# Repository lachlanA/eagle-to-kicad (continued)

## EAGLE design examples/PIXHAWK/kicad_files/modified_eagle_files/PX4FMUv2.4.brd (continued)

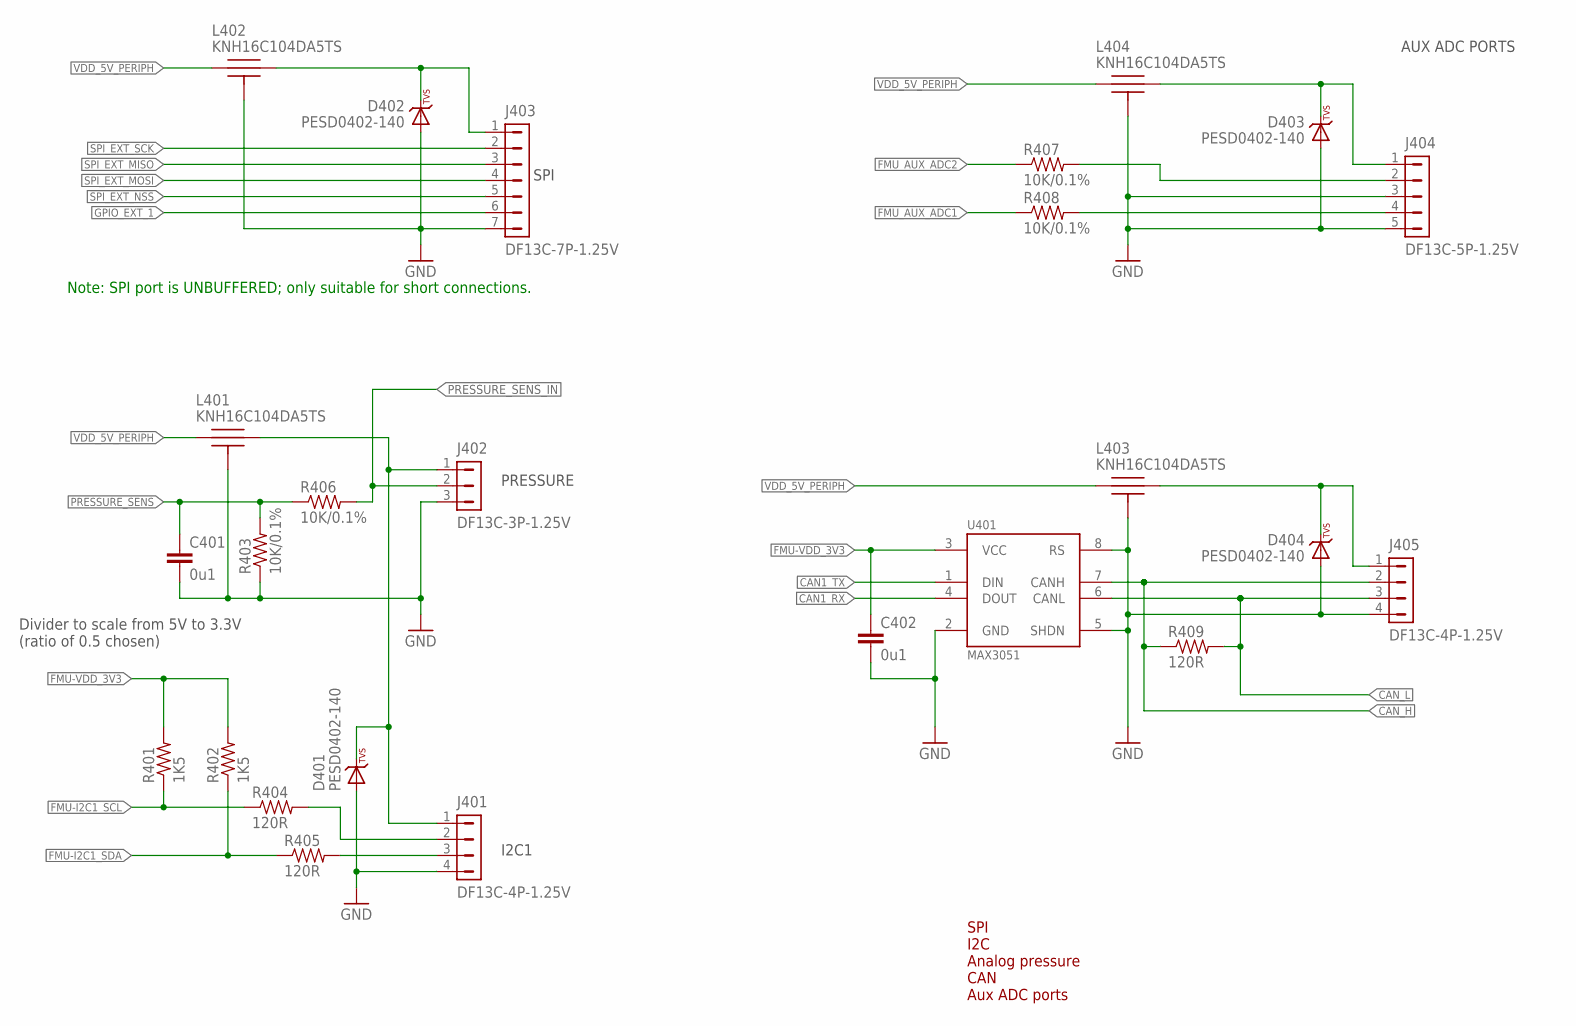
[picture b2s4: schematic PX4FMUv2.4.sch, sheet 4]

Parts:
C401, C402: 0u1; 0402-CAP; PARTNO CC0402ZRY5V7BB104
D401, D402, D403, D404: PESD0402-140; 0402-TVS; PARTNO PESD0402-140
J401, J405: DF13C-4P-1.25V; PARTNO DF13C-4P-1.25V(20)
J402: DF13C-3P-1.25V; PARTNO DF13C-3P-1.25V(20)
J403: DF13C-7P-1.25V; PARTNO DF13C-7P-1.25V(20)
J404: DF13C-5P-1.25V; PARTNO DF13C-5P-1.25V(20)
L401, L402, L403, L404: KNH16C104DA5TS; KYOCERA-KNH16-DA; PARTNO KNH16C104DA5TS
R401, R402: 1K5; 0402-RES; PARTNO RC0402FR-071K5L
R403, R406, R407, R408: 10K/0.1%; 0402-RES; PARTNO ERA-2AEB103X
R404, R405, R409: 120R; 0402-RES; PARTNO RC0402FR-07120RL
U401: MAX3051; SOT23-8; PARTNO MAX3051EKA

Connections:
!SPI_EXT_NSS: J403.5; also elsewhere on the board
CAN1_RX: U401.4 (DOUT); also elsewhere on the board
CAN1_TX: U401.1 (DIN); also elsewhere on the board
CAN_H: J405.2, R409.P$1 (1), U401.7 (CANH); also elsewhere on the board
CAN_L: J405.3, R409.P$2 (2), U401.6 (CANL); also elsewhere on the board
FMU-I2C1_SCL: R401.P$1 (1), R404.P$1 (1); also elsewhere on the board
FMU-I2C1_SDA: R402.P$1 (1), R405.P$1 (1); also elsewhere on the board
FMU-VDD_3V3: C402.P$1 (1), R401.P$2 (2), R402.P$2 (2), U401.3 (VCC); also elsewhere on the board
FMU_AUX_ADC1: R408.P$1 (1); also elsewhere on the board
FMU_AUX_ADC1_PROT: J404.4, R408.P$2 (2)
FMU_AUX_ADC2: R407.P$1 (1); also elsewhere on the board
FMU_AUX_ADC2_PROT: J404.2, R407.P$2 (2)
GND: C401.P$2 (2), C402.P$2 (2), D401.A, D402.A, D403.A, D404.A, J401.4, J402.3, J403.7, J404.3, J404.5, J405.4, L401.P$3, L401.P$4, L401.P$5, L402.P$3, L402.P$4, L402.P$5, L403.P$3, L403.P$4, L403.P$5, L404.P$3, L404.P$4, L404.P$5, R403.P$1 (1), U401.2 (GND), U401.5 (SHDN), U401.8 (RS); also elsewhere on the board
GPIO_EXT_1: J403.6; also elsewhere on the board
unnamed: J401.2, R404.P$2 (2)
unnamed: J401.3, R405.P$2 (2)
unnamed: D402.C, J403.1, L402.P$2
unnamed: D401.C, J401.1, J402.1, L401.P$2
unnamed: D404.C, J405.1, L403.P$2
unnamed: D403.C, J404.1, L404.P$2
PRESSURE_SENS: C401.P$1 (1), R403.P$2 (2), R406.P$1 (1); also elsewhere on the board
PRESSURE_SENS_IN: J402.2, R406.P$2 (2); also elsewhere on the board
SPI_EXT_MISO: J403.3; also elsewhere on the board
SPI_EXT_MOSI: J403.4; also elsewhere on the board
SPI_EXT_SCK: J403.2; also elsewhere on the board
VDD_5V_PERIPH: L401.P$1, L402.P$1, L403.P$1, L404.P$1; also elsewhere on the board

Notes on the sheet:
SPI
PRESSURE
I2C1
AUX ADC PORTS
SPI I2C Analog pressure CAN Aux ADC ports
Note: SPI port is UNBUFFERED; only suitable for short connections.
Divider to scale from 5V to 3.3V (ratio of 0.5 chosen)

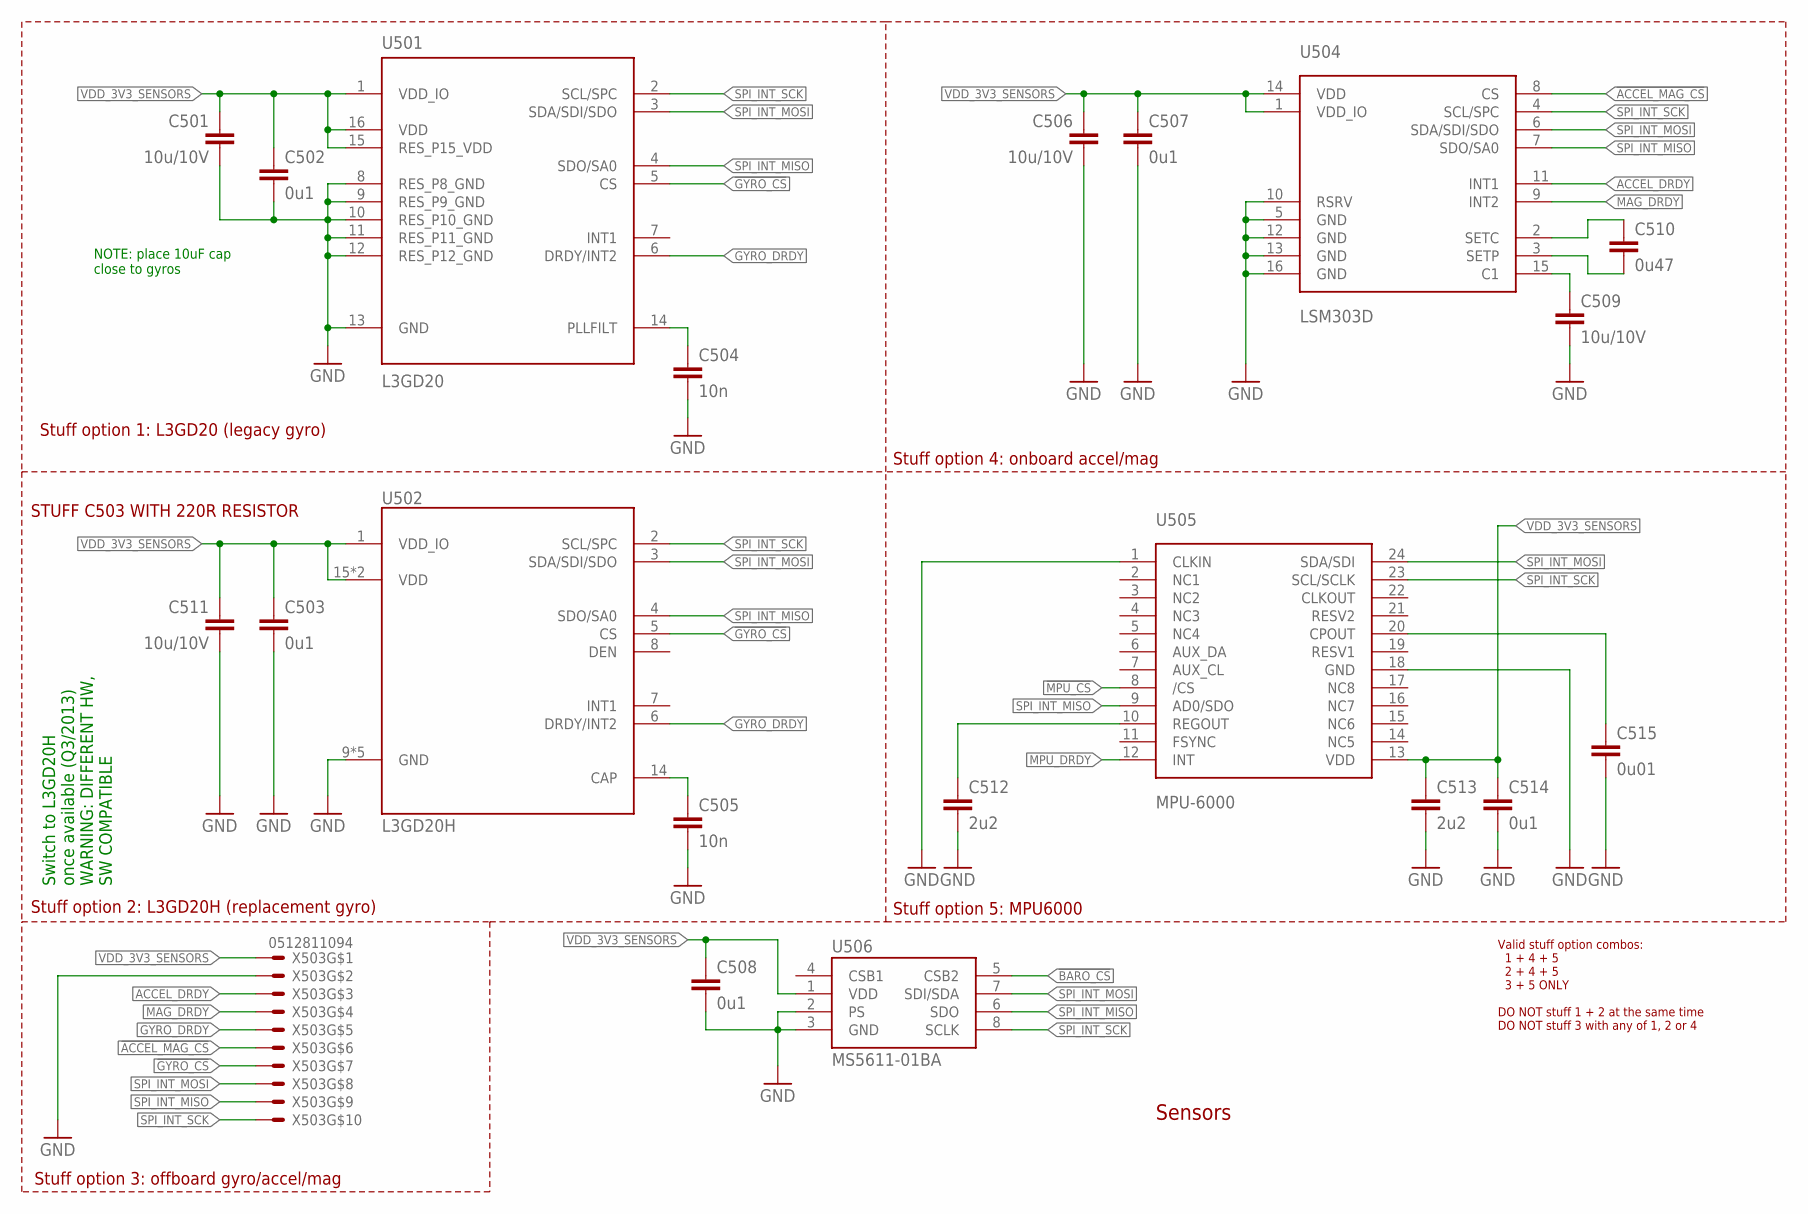
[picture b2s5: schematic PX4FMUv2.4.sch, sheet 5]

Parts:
C501, C506, C509, C511: 10u/10V; 0805-CAP; PARTNO CC0805ZKY5V6BB106
C502, C503, C507, C508, C514: 0u1; 0402-CAP; PARTNO CC0402ZRY5V7BB104
C504, C505: 10n; 0402-CAP; PARTNO CC0402KRX7R7BB103
C510: 0u47; 0402-CAP; PARTNO C1005X5R1C474K050BC
C512, C513: 2u2; 0603-CAP; PARTNO CC0402ZRY5V7BB104
C515: 0u01; 0603-CAP; PARTNO GRM155R71E103JA01J
U501: L3GD20; L3G4200DH-MAN; PARTNO L3GD20
U502: L3GD20H; LGA-16L; PARTNO L3GD20H
U504: LSM303D; LGA-16L; PARTNO LSM303D
U505: MPU-6000; QFN-24; PARTNO MPU-6000
U506: MS5611-01BA; PARTNO MS5611-01BA
X503: 0512811094; 51281-1094; PARTNO 0781191109

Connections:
!ACCEL_MAG_CS: U504.8 (CS), X503.6; also elsewhere on the board
!BARO_CS: U506.5 (CSB2); also elsewhere on the board
!GYRO_CS: U501.5 (CS), U502.5 (CS), X503.7; also elsewhere on the board
!MPU_CS: U505.8 (/CS); also elsewhere on the board
ACCEL_DRDY: U504.11 (INT1), X503.3; also elsewhere on the board
GND: C501.P$2 (2), C502.P$2 (2), C503.P$2 (2), C504.P$2 (2), C505.P$2 (2), C506.P$2 (2), C507.P$2 (2), C508.P$2 (2), C509.P$2 (2), C511.P$2 (2), C512.P$2 (2), C513.P$2 (2), C514.P$2 (2), C515.P$2 (2), U501.8 (RES_P8_GND), U501.9 (RES_P9_GND), U501.10 (RES_P10_GND), U501.11 (RES_P11_GND), U501.12 (RES_P12_GND), U501.13 (GND), U502.9 (GND), U502.10 (GND), U502.11 (GND), U502.12 (GND), U502.13 (GND), U504.5 (GND), U504.10 (RSRV), U504.12 (GND), U504.13 (GND), U504.16 (GND), U505.1 (CLKIN), U505.18 (GND), U506.2 (PS), U506.3 (GND), X503.2; also elsewhere on the board
GYRO_DRDY: U501.6 (DRDY/INT2), U502.6 (DRDY/INT2), X503.5; also elsewhere on the board
MAG_DRDY: U504.9 (INT2), X503.4; also elsewhere on the board
MPU_DRDY: U505.12 (INT); also elsewhere on the board
unnamed: C509.P$1 (1), U504.15 (C1)
unnamed: C510.P$1 (1), U504.2 (SETC)
unnamed: C510.P$2 (2), U504.3 (SETP)
unnamed: C505.P$1 (1), U502.14 (CAP)
unnamed: C504.P$1 (1), U501.14 (PLLFILT)
unnamed: C512.P$1 (1), U505.10 (REGOUT)
unnamed: C515.P$1 (1), U505.20 (CPOUT)
SPI_INT_MISO: U501.4 (SDO/SA0), U502.4 (SDO/SA0), U504.7 (SDO/SA0), U505.9 (AD0/SDO), U506.6 (SDO), X503.9; also elsewhere on the board
SPI_INT_MOSI: U501.3 (SDA/SDI/SDO), U502.3 (SDA/SDI/SDO), U504.6 (SDA/SDI/SDO), U505.24 (SDA/SDI), U506.7 (SDI/SDA), X503.8; also elsewhere on the board
SPI_INT_SCK: U501.2 (SCL/SPC), U502.2 (SCL/SPC), U504.4 (SCL/SPC), U505.23 (SCL/SCLK), U506.8 (SCLK), X503.10; also elsewhere on the board
VDD_3V3_SENSORS: C501.P$1 (1), C502.P$1 (1), C503.P$1 (1), C506.P$1 (1), C507.P$1 (1), C508.P$1 (1), C511.P$1 (1), C513.P$1 (1), C514.P$1 (1), U501.1 (VDD_IO), U501.15 (RES_P15_VDD), U501.16 (VDD), U502.1 (VDD_IO), U502.15 (VDD), U502.16 (VDD), U504.1 (VDD_IO), U504.14 (VDD), U505.13 (VDD), U506.1 (VDD), X503.1; also elsewhere on the board

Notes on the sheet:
Sensors
Switch to L3GD20H once available (Q3/2013) WARNING: DIFFERENT HW, SW COMPATIBLE
NOTE: place 10uF cap close to gyros
Stuff option 1: L3GD20 (legacy gyro)
Stuff option 2: L3GD20H (replacement gyro)
Stuff option 4: onboard accel/mag
Valid stuff option combos: 1 + 4 + 5 2 + 4 + 5 3 + 5 ONLY DO NOT stuff 1 + 2 at the same time DO NOT stuff 3 with any of 1, 2 or 4
Stuff option 5: MPU6000
Stuff option 3: offboard gyro/accel/mag
STUFF C503 WITH 220R RESISTOR

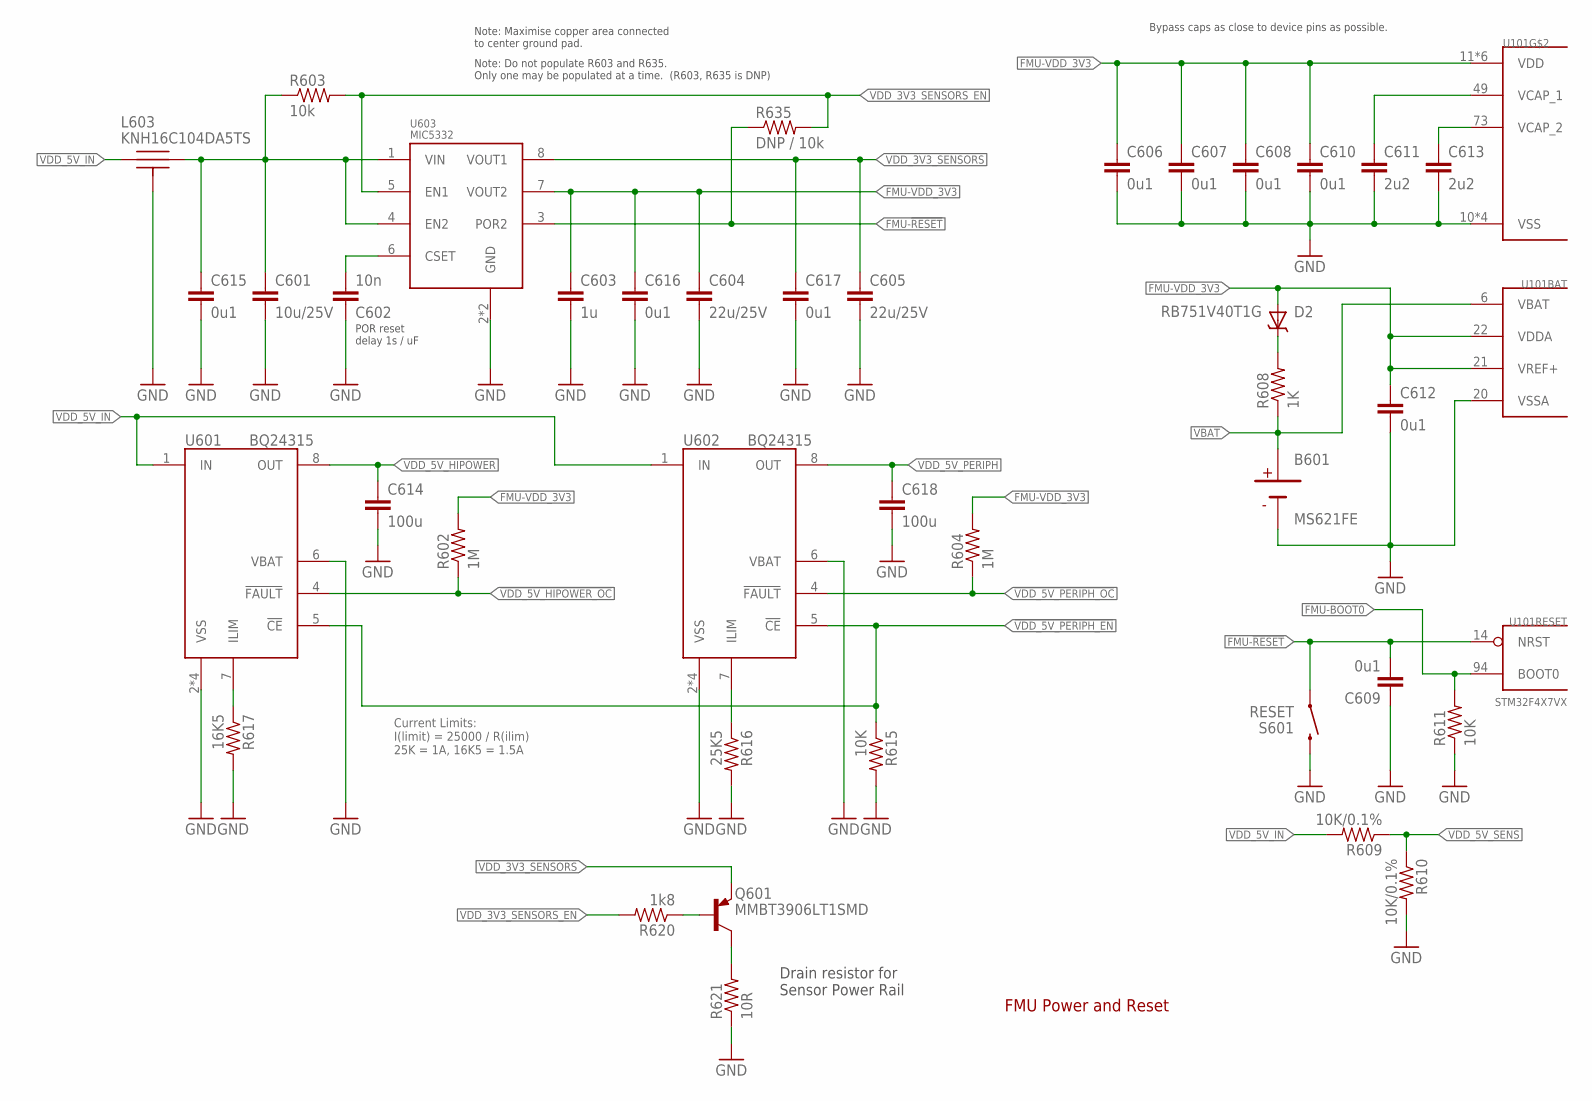
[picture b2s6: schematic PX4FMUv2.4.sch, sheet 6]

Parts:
B601: MS621FE; PARTNO MS621FE-FL11E
C601: 10u/25V; 0805-CAP; PARTNO CL21A106KAYNNNE
C602: 10n; 0402-CAP; PARTNO CC0402KRX7R7BB103
C603: 1u; 0603-CAP; PARTNO CC0603ZRY5V7BB105
C604, C605: 22u/25V; 0805-CAP; PARTNO CL21A226MAQNNNE
C606, C607, C608, C609, C610, C612, C615, C616, C617: 0u1; 0402-CAP; PARTNO CC0402ZRY5V7BB104
C611, C613: 2u2; 0603-CAP; PARTNO C1608Y5V1C225Z
C614, C618: 100u; 1206-CAP; PARTNO C3216X5R1A107M160AC
D2: RB751V40T1G; SOD323; PARTNO RB751V40T1G
L603: KNH16C104DA5TS; KYOCERA-KNH16-DA; PARTNO KNH16C104DA5TS
Q601: MMBT3906LT1SMD; SOT23-BEC; PARTNO MMBT 3906 LT1
R602, R604: 1M; 0402-RES; PARTNO RC0402FR-071ML
R603: 10k; 0402-RES; PARTNO RC0402FR-0710KL
R608: 1K; 0402-RES; PARTNO RC0402FR-071KL
R609, R610: 10K/0.1%; 0402-RES; PARTNO ERA-2AEB103X
R611, R615: 10K; 0402-RES; PARTNO RC0402FR-0710KL
R616: 25K5; 0402-RES; PARTNO RMCF0402FT25K5
R617: 16K5; 0402-RES; PARTNO RMCF0402FT16K5
R620: 1k8; 0402-RES; PARTNO RC1005F182CS
R621: 10R; 0603-RES; PARTNO RC1608J100CS
R635: DNP / 10k; 0402-RES; PARTNO RC0402FR-0710KL
S601: RESET; EVQP7J01K; PARTNO EVQP7J01K
U101: STM32F4X7VX; TQFP100; PARTNO STM32F427VI
U601, U602: BQ24315; QFN8-DSG; PARTNO BQ24315DSGR
U603: MIC5332; MLF-8-EPAD; PARTNO MIC5332-SSYMT

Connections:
!VDD_5V_HIPOWER_OC: R602.P$1 (1), U601.4 (!FAULT); also elsewhere on the board
!VDD_5V_PERIPH_EN: R615.P$1 (1), U601.5 (!CE), U602.5 (!CE); also elsewhere on the board
!VDD_5V_PERIPH_OC: R604.P$1 (1), U602.4 (!FAULT); also elsewhere on the board
FMU-!RESET: C609.P$2 (2), R635.P$1 (1), S601.A1 (1), U101.14 (NRST), U603.3 (POR2); also elsewhere on the board
FMU-BOOT0: R611.P$2 (2), U101.94 (BOOT0); also elsewhere on the board
FMU-VDD_3V3: C603.P$1 (1), C604.P$1 (1), C606.P$1 (1), C607.P$1 (1), C608.P$1 (1), C610.P$1 (1), C612.P$1 (1), C616.P$1 (1), D2.A, R602.P$2 (2), R604.P$2 (2), U101.11 (VDD), U101.19 (VDD), U101.21 (VREF+), U101.22 (VDDA), U101.28 (VDD), U101.50 (VDD), U101.75 (VDD), U101.100 (VDD), U603.7 (VOUT2); also elsewhere on the board
FMU-VDD_5V5: C601.P$1 (1), C615.P$1 (1), L603.P$2, R603.P$1 (1), U603.1 (VIN), U603.4 (EN2)
GND: B601.2 (NEG), C601.P$2 (2), C602.P$1 (1), C603.P$2 (2), C604.P$2 (2), C605.P$2 (2), C606.P$2 (2), C607.P$2 (2), C608.P$2 (2), C609.P$1 (1), C610.P$2 (2), C611.P$2 (2), C612.P$2 (2), C613.P$2 (2), C614.P$2 (2), C615.P$2 (2), C616.P$2 (2), C617.P$2 (2), C618.P$2 (2), L603.P$3, L603.P$4, L603.P$5, R610.P$2 (2), R611.P$1 (1), R615.P$2 (2), R616.P$2 (2), R617.P$2 (2), R621.1, S601.B3 (2), U101.10 (VSS), U101.20 (VSSA), U101.27 (VSS), U101.74 (VSS), U101.99 (VSS), U601.2 (VSS), U601.6 (VBAT), U601.GND (VSS), U601.P$2 (VSS), U601.P$3 (VSS), U602.2 (VSS), U602.6 (VBAT), U602.GND (VSS), U602.P$2 (VSS), U602.P$3 (VSS), U603.2 (GND), U603.GND; also elsewhere on the board
unnamed: C613.P$1 (1), U101.73 (VCAP_2)
unnamed: C602.P$2 (2), U603.6 (CSET)
unnamed: C611.P$1 (1), U101.49 (VCAP_1)
unnamed: D2.C, R608.P$2 (2)
unnamed: R616.P$1 (1), U602.7 (ILIM)
unnamed: Q601.C, R621.2
unnamed: Q601.B, R620.P$1 (1)
unnamed: R617.P$1 (1), U601.7 (ILIM)
VBAT: B601.1 (POS), R608.P$1 (1), U101.6 (VBAT); also elsewhere on the board
VDD_3V3_SENSORS: C605.P$1 (1), C617.P$1 (1), Q601.E, U603.8 (VOUT1); also elsewhere on the board
VDD_3V3_SENSORS_EN: R603.P$2 (2), R620.P$2 (2), R635.P$2 (2), U603.5 (EN1); also elsewhere on the board
VDD_5V_HIPOWER: C614.P$1 (1), U601.8 (OUT); also elsewhere on the board
VDD_5V_IN: L603.P$1, R609.P$2 (2), U601.1 (IN), U602.1 (IN); also elsewhere on the board
VDD_5V_PERIPH: C618.P$1 (1), U602.8 (OUT); also elsewhere on the board
VDD_5V_SENS: R609.P$1 (1), R610.P$1 (1); also elsewhere on the board

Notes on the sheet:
FMU Power and Reset
Bypass caps as close to device pins as possible.
Note: Maximise copper area connected to center ground pad.
POR reset delay 1s / uF
Current Limits: I(limit) = 25000 / R(ilim) 25K = 1A, 16K5 = 1.5A
Drain resistor for Sensor Power Rail
Note: Do not populate R603 and R635. Only one may be populated at a time. (R603, R635 is DNP)

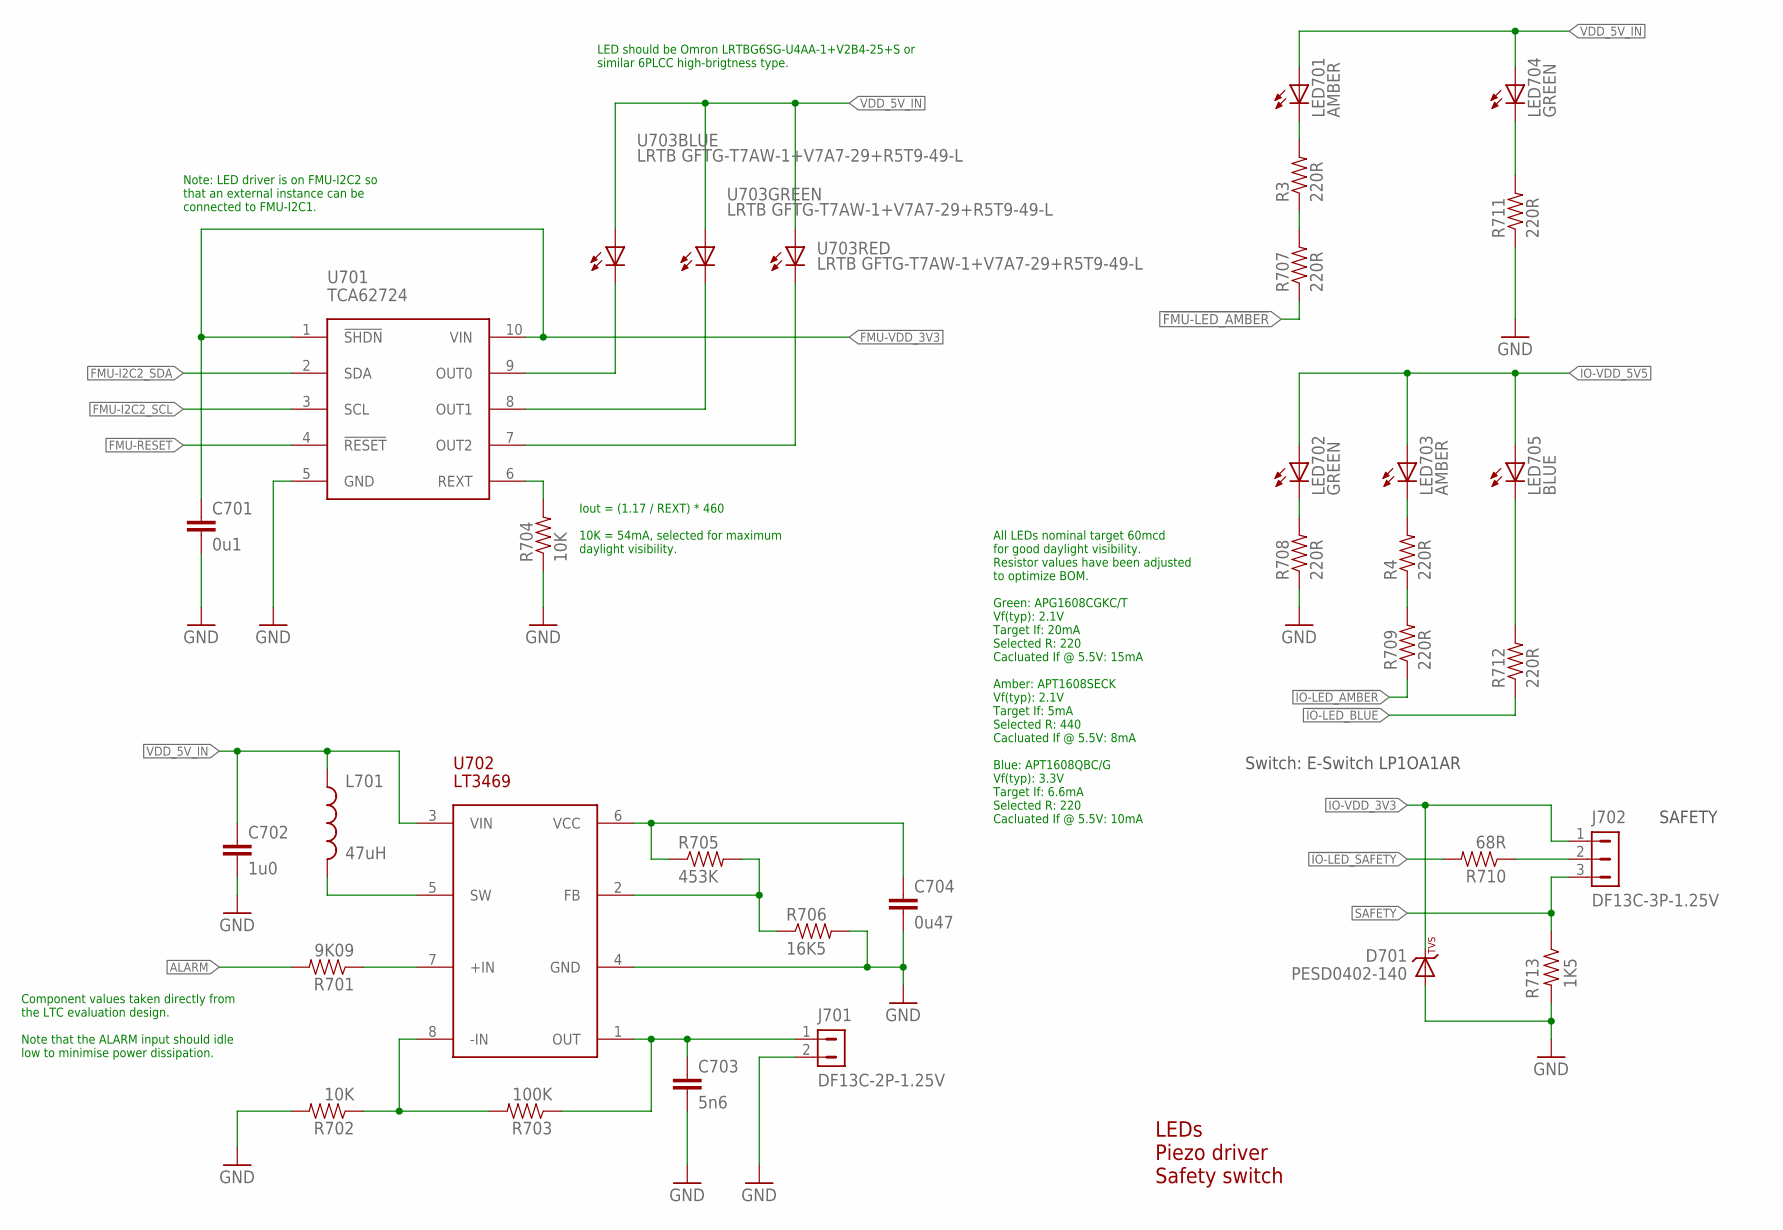
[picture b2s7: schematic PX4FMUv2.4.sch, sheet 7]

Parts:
C701: 0u1; 0402-CAP; PARTNO CC0402ZRY5V7BB104
C702: 1u0; 0603-CAP; PARTNO CC0603ZRY5V7BB105
C703: 5n6; 0402-CAP; PARTNO CC0402KRX7R7BB562
C704: 0u47; 0402-CAP; PARTNO C1005X5R1C474K050BC
D701: PESD0402-140; 0402-TVS; PARTNO PESD0402-140
J701: DF13C-2P-1.25V; PARTNO DF13C-2P-1.25V(20)
J702: DF13C-3P-1.25V; PARTNO DF13C-3P-1.25V(20)
L701: 47uH; 0805-IND; PARTNO MLZ2012M470W
LED701, LED703: AMBER; 0603-LED; PARTNO APTD1608SECK
LED702, LED704: GREEN; 0603-LED; PARTNO APTD1608CGCK
LED705: BLUE; 0603-LED; PARTNO APTD1608QBC/D
R3, R4, R707, R708, R709, R711, R712: 220R; 0402-RES; PARTNO RC0402FR-07220RL
R701: 9K09; 0402-RES; PARTNO RMCF0402FT9K09
R702, R704: 10K; 0402-RES; PARTNO RC0402FR-0710KL
R703: 100K; 0402-RES; PARTNO RC0402FR-07100KL
R705: 453K; 0402-RES; PARTNO RMCF0402FT453K
R706: 16K5; 0402-RES; PARTNO RMCF0402FT16K5
R710: 68R; 0402-RES; PARTNO ERJ-2GEJ680X
R713: 1K5; 0402-RES; PARTNO RC0402FR-071K5L
U701: TCA62724FMG; SON10; PARTNO TCA62724FMG
U702: LT3469; SOT23-8; PARTNO LT3469ETS8
U703: LRTB GFTG-T7AW-1+V7A7-29+R5T9-49-L; 6-PLCC; PARTNO LRTB GFTG-T7AW-1+V7A7-29+R5T9-49-L

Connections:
!FMU-LED_AMBER: R707.P$1 (1); also elsewhere on the board
!IO-LED_AMBER: R709.P$1 (1); also elsewhere on the board
!IO-LED_BLUE: R712.P$1 (1); also elsewhere on the board
!IO-LED_SAFETY: R710.P$2 (2); also elsewhere on the board
ALARM: R701.P$2 (2); also elsewhere on the board
FMU-!RESET: U701.4 (!RESET); also elsewhere on the board
FMU-I2C2_SCL: U701.3 (SCL); also elsewhere on the board
FMU-I2C2_SDA: U701.2 (SDA); also elsewhere on the board
FMU-VDD_3V3: C701.P$1 (1), U701.1 (!SHDN), U701.10 (VIN); also elsewhere on the board
GND: C701.P$2 (2), C702.P$2 (2), C703.P$2 (2), C704.P$2 (2), D701.A, J701.2, R702.P$2 (2), R704.P$1 (1), R706.P$2 (2), R708.P$1 (1), R711.P$1 (1), R713.P$2 (2), U701.5 (GND), U702.4 (GND); also elsewhere on the board
IO-VDD_3V3: D701.C, J702.1; also elsewhere on the board
IO-VDD_5V5: LED702.A, LED703.A, LED705.A; also elsewhere on the board
unnamed: LED704.C, R711.P$2 (2)
unnamed: LED705.C, R712.P$2 (2)
unnamed: R3.P$1 (1), R707.P$2 (2)
unnamed: R705.P$2 (2), R706.P$1 (1), U702.2 (FB)
unnamed: R702.P$1 (1), R703.P$2 (2), U702.8 (-IN)
unnamed: LED701.C, R3.P$2 (2)
unnamed: C703.P$1 (1), J701.1, R703.P$1 (1), U702.1 (OUT)
unnamed: R701.P$1 (1), U702.7 (+IN)
unnamed: LED702.C, R708.P$2 (2)
unnamed: L701.P$2 (2), U702.5 (SW)
unnamed: C704.P$1 (1), R705.P$1 (1), U702.6 (VCC)
unnamed: R4.P$1 (1), R709.P$2 (2)
unnamed: LED703.C, R4.P$2 (2)
unnamed: J702.2, R710.P$1 (1)
unnamed: R704.P$2 (2), U701.6 (REXT)
RGB_LED_3: U701.9 (OUT0), U703.C1 (C)
RGB_LED_4: U701.8 (OUT1), U703.C2 (C)
RGB_LED_14: U701.7 (OUT2), U703.C3 (C)
SAFETY: J702.3, R713.P$1 (1); also elsewhere on the board
VDD_5V_IN: C702.P$1 (1), L701.P$1 (1), LED701.A, LED704.A, U702.3 (VIN), U703.A1 (A), U703.A2 (A), U703.A3 (A); also elsewhere on the board

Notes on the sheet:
LEDs Piezo driver Safety switch
Switch: E-Switch LP1OA1AR
SAFETY
LED should be Omron LRTBG6SG-U4AA-1+V2B4-25+S or similar 6PLCC high-brigtness type.
Iout = (1.17 / REXT) * 460 10K = 54mA, selected for maximum daylight visibility.
Note: LED driver is on FMU-I2C2 so that an external instance can be connected to FMU-I2C1.
All LEDs nominal target 60mcd for good daylight visibility. Resistor values have been adjusted to optimize BOM. Green: APG1608CGKC/T Vf(typ): 2.1V Target If: 20mA Selected R: 220 Cacluated If @ 5.5V: 15mA Amber: APT1608SECK Vf(typ): 2.1V Target If: 5mA Selected R: 440 Cacluated If @ 5.5V: 8mA Blue: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
Component values taken directly from the LTC evaluation design. Note that the ALARM input should idle low to minimise power dissipation.

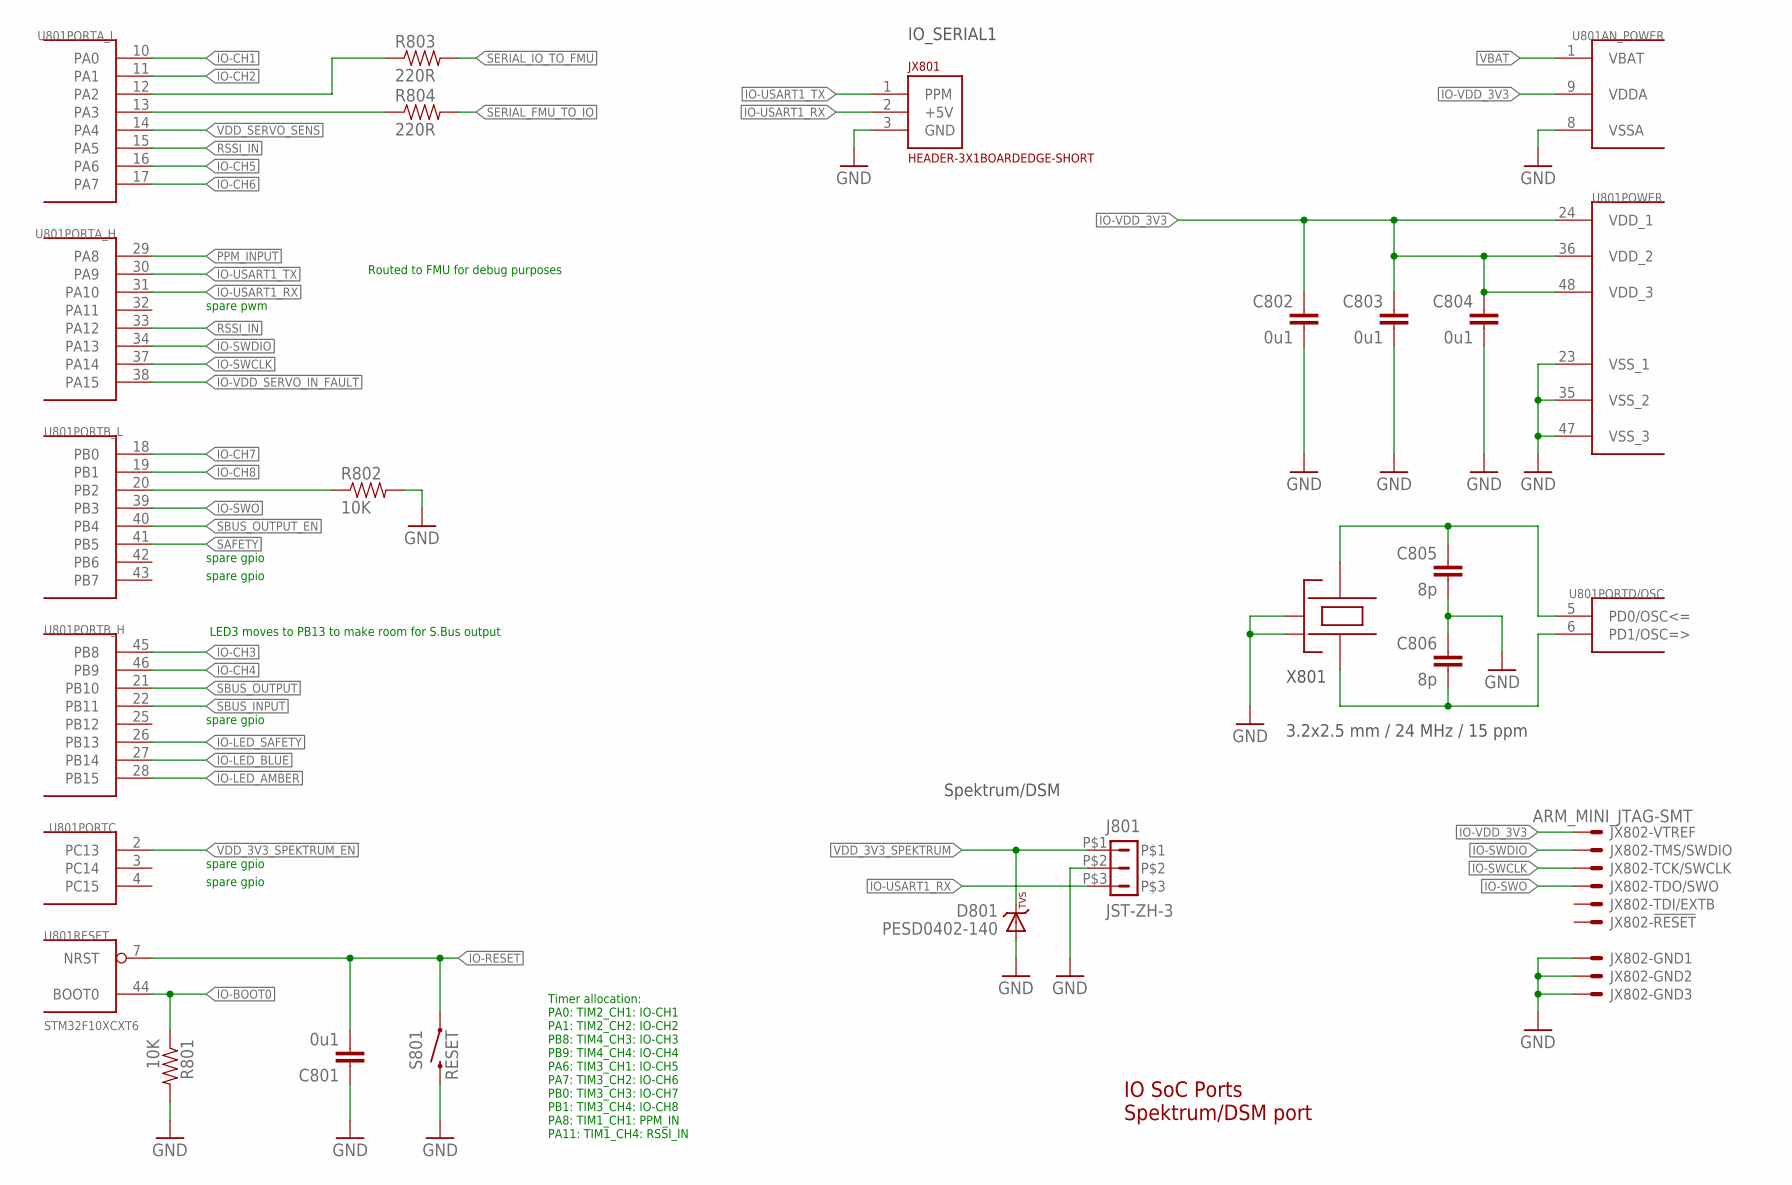
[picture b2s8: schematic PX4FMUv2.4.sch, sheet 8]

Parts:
C801, C802, C803, C804: 0u1; 0402-CAP; PARTNO CC0402ZRY5V7BB104
C805, C806: 8p; 0402-CAP; PARTNO C1005C0G1H080C
D801: PESD0402-140; 0402-TVS; PARTNO PESD0402-140
J801: JST-ZH-3; JST-ZH-SMT-VERTICAL; PARTNO B3B-ZR-SM4-TF (LF)(SN)(P)
JX801: HEADER-3X1BOARDEDGE-SHORT; HEADER_3X01_SMD_H_BOARD_EDGE_SHORT
JX802: ARM_MINI_JTAG-SMT; FTSH-105-01-XXX-DV-K; PARTNO M50-3900542
R801, R802: 10K; 0402-RES; PARTNO RC0402FR-0710KL
R803, R804: 220R; 0402-RES; PARTNO RC0402FR-07220RL
S801: RESET; EVQP7J01K; PARTNO EVQP7J01K
U801: STM32F10XCXT6; TQFP48; PARTNO STM32F100C8T6B
X801: 3.2x2.5 mm / 24 MHz / 15 ppm; OSCILLATOR-3.2X2.5; PARTNO NX3225SA-24.000000MHZ

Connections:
!IO-LED_AMBER: U801.28 (PB15); also elsewhere on the board
!IO-LED_BLUE: U801.27 (PB14); also elsewhere on the board
!IO-LED_SAFETY: U801.26 (PB13); also elsewhere on the board
!SBUS_OUTPUT_EN: U801.40 (PB4); also elsewhere on the board
GND: C801.P$1 (1), C802.P$2 (2), C803.P$2 (2), C804.P$2 (2), C805.P$2 (2), C806.P$1 (1), D801.A, J801.P$2, JX801.3 (GND), JX802.3, JX802.5, JX802.9, R801.P$2 (2), R802.P$2 (2), S801.B3 (2), U801.8 (VSSA), U801.23 (VSS_1), U801.35 (VSS_2), U801.47 (VSS_3), X801.2 (NC_2), X801.4 (NC_4); also elsewhere on the board
IO-!RESET: C801.P$2 (2), S801.A1 (1), U801.7 (NRST); also elsewhere on the board
IO-!VDD_SERVO_IN_FAULT: U801.38 (PA15); also elsewhere on the board
IO-BOOT0: R801.P$1 (1), U801.44 (BOOT0); also elsewhere on the board
IO-BOOT1: R802.P$1 (1), U801.20 (PB2)
IO-CH1: U801.10 (PA0); also elsewhere on the board
IO-CH2: U801.11 (PA1); also elsewhere on the board
IO-CH3: U801.45 (PB8); also elsewhere on the board
IO-CH4: U801.46 (PB9); also elsewhere on the board
IO-CH5: U801.16 (PA6); also elsewhere on the board
IO-CH6: U801.17 (PA7); also elsewhere on the board
IO-CH7: U801.18 (PB0); also elsewhere on the board
IO-CH8: U801.19 (PB1); also elsewhere on the board
IO-SWCLK: JX802.4, U801.37 (PA14)
IO-SWDIO: JX802.2, U801.34 (PA13)
IO-SWO: JX802.6, U801.39 (PB3)
IO-USART1_RX: J801.P$3, JX801.2 (+5V), U801.31 (PA10)
IO-USART1_TX: JX801.1 (PPM), U801.30 (PA9); also elsewhere on the board
IO-VDD_3V3: C802.P$1 (1), C803.P$1 (1), C804.P$1 (1), JX802.1, U801.9 (VDDA), U801.24 (VDD_1), U801.36 (VDD_2), U801.48 (VDD_3); also elsewhere on the board
unnamed: R803.P$1 (1), U801.12 (PA2)
unnamed: R804.P$1 (1), U801.13 (PA3)
unnamed: C806.P$2 (2), U801.6 (PD1/OSC=>), X801.1
unnamed: C805.P$1 (1), U801.5 (PD0/OSC<=), X801.3
PPM_INPUT: U801.29 (PA8); also elsewhere on the board
RSSI_IN: U801.15 (PA5), U801.33 (PA12); also elsewhere on the board
SAFETY: U801.41 (PB5); also elsewhere on the board
SBUS_INPUT: U801.22 (PB11); also elsewhere on the board
SBUS_OUTPUT: U801.21 (PB10); also elsewhere on the board
SERIAL_FMU_TO_IO: R804.P$2 (2); also elsewhere on the board
SERIAL_IO_TO_FMU: R803.P$2 (2); also elsewhere on the board
VBAT: U801.1 (VBAT); also elsewhere on the board
VDD_3V3_SPEKTRUM: D801.C, J801.P$1; also elsewhere on the board
VDD_3V3_SPEKTRUM_EN: U801.2 (PC13); also elsewhere on the board
VDD_SERVO_SENS: U801.14 (PA4); also elsewhere on the board

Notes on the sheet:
IO SoC Ports Spektrum/DSM port
LED3 moves to PB13 to make room for S.Bus output
Routed to FMU for debug purposes
IO_SERIAL1
Spektrum/DSM
Timer allocation: PA0: TIM2_CH1: IO-CH1 PA1: TIM2_CH2: IO-CH2 PB8: TIM4_CH3: IO-CH3 PB9: TIM4_CH4: IO-CH4 PA6: TIM3_CH1: IO-CH5 PA7: TIM3_CH2: IO-CH6 PB0: TIM3_CH3: IO-CH7 PB1: TIM3_CH4: IO-CH8 PA8: TIM1_CH1: PPM_IN PA11: TIM1_CH4: RSSI_IN
spare pwm
spare gpio

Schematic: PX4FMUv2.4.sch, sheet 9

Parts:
C901, C902, C903: 0u1; 0402-CAP; PARTNO CC0402ZRY5V7BB104
D1: MSS1P4-M3; MICROSMP; PARTNO MSS1P4-M3/89A
D901, D902, D903: PESD0402-140; 0402-TVS; PARTNO PESD0402-140
J901: HEADER-3X163X16RA; 3X16RA
L901: KNH16C104DA5TS; KYOCERA-KNH16-DA; PARTNO KNH16C104DA5TS
R901: 10K; 0402-RES; PARTNO RC0402FR-0710KL
R902, R903, R904, R905, R906, R907, R908, R909, R910, R911, R912, R913, R914, R915, R916, R917: 220R; 0402-RES; PARTNO RC0402FR-07220RL
R918, R919, R922: 10K/0.1%; 0402-RES; PARTNO ERA-2AEB103X
U901, U902: TXS0108QFN20; QFN20-RGY; PARTNO TXS0108ERGYR
U903: 74LVC2G240; TSSOP8_SOT505-2; PARTNO 74LVC2G240DP,125

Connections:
!SBUS_OUTPUT_EN: U903.7 (!2OE); also elsewhere on the board
FMU-CH1: U901.7 (A6); also elsewhere on the board
FMU-CH1-PROT: J901.46, R913.P$2 (2)
FMU-CH2: U901.6 (A5); also elsewhere on the board
FMU-CH3: U901.5 (A4); also elsewhere on the board
FMU-CH4: U901.4 (A3); also elsewhere on the board
FMU-CH5: U901.3 (A2); also elsewhere on the board
FMU-CH6: U901.1 (A1); also elsewhere on the board
FMU-CH6-PROT: J901.31, R902.P$2 (2)
FMU-VDD_3V3: C902.P$1 (1), U901.2 (VCCA), U901.10 (OE), U901.19 (VCCB); also elsewhere on the board
GND: C901.P$2 (2), C902.P$2 (2), C903.P$2 (2), D901.A, D902.A, D903.A, J901.3, J901.6, J901.9, J901.12, J901.15, J901.18, J901.21, J901.24, J901.27, J901.30, J901.33, J901.36, J901.39, J901.42, J901.45, J901.48, L901.P$3, L901.P$4, L901.P$5, R919.P$1 (1), U901.11 (GND), U902.11 (GND), U903.1 (!1OE), U903.4 (GND); also elsewhere on the board
IO-CH1: U902.9 (A8); also elsewhere on the board
IO-CH1-PROT: J901.28, R917.P$2 (2)
IO-CH2: U902.8 (A7); also elsewhere on the board
IO-CH3: U902.7 (A6); also elsewhere on the board
IO-CH4: U902.6 (A5); also elsewhere on the board
IO-CH5: U902.5 (A4); also elsewhere on the board
IO-CH6: U902.4 (A3); also elsewhere on the board
IO-CH7: U902.3 (A2); also elsewhere on the board
IO-CH8: U902.1 (A1); also elsewhere on the board
IO-CH8-PROT: J901.7, R905.P$2 (2)
IO-VDD_3V3: C901.P$1 (1), C903.P$1 (1), U902.2 (VCCA), U902.10 (OE), U902.19 (VCCB), U903.8 (VCC); also elsewhere on the board
IO-VDD_5V5: J901.2; also elsewhere on the board
unnamed: R918.P$2 (2), R922.P$1 (1)
unnamed: J901.10, R914.P$2 (2)
unnamed: D902.C, R901.P$2 (2), R910.P$1 (1), U903.3 (2Y)
unnamed: R905.P$1 (1), U902.20 (B1)
unnamed: R914.P$1 (1), U902.18 (B2)
unnamed: R906.P$1 (1), U902.17 (B3)
unnamed: R915.P$1 (1), U902.16 (B4)
unnamed: R907.P$1 (1), U902.15 (B5)
unnamed: R916.P$1 (1), U902.14 (B6)
unnamed: R908.P$1 (1), U902.13 (B7)
unnamed: R917.P$1 (1), U902.12 (B8)
unnamed: R902.P$1 (1), U901.20 (B1)
unnamed: R911.P$1 (1), U901.18 (B2)
unnamed: R903.P$1 (1), U901.17 (B3)
unnamed: R912.P$1 (1), U901.16 (B4)
unnamed: R904.P$1 (1), U901.15 (B5)
unnamed: R913.P$1 (1), U901.14 (B6)
unnamed: J901.34, R911.P$2 (2)
unnamed: J901.13, R906.P$2 (2)
unnamed: J901.16, R915.P$2 (2)
unnamed: J901.19, R907.P$2 (2)
unnamed: J901.22, R916.P$2 (2)
unnamed: J901.25, R908.P$2 (2)
unnamed: J901.37, R903.P$2 (2)
unnamed: J901.40, R912.P$2 (2)
unnamed: J901.43, R904.P$2 (2)
unnamed: J901.4, R910.P$2 (2)
unnamed: D1.CATHODE (C), D903.C, L901.P$1
PPM-SBUS-PROT: J901.1, R909.P$2 (2)
PPM_INPUT: D901.C, R909.P$1 (1), U903.2 (1A); also elsewhere on the board
RSSI_IN: R901.P$1 (1); also elsewhere on the board
SBUS_INPUT: U903.6 (1Y); also elsewhere on the board
SBUS_OUTPUT: U903.5 (2A); also elsewhere on the board
VDD_SERVO: D1.ANODE (A), J901.5, J901.8, J901.11, J901.14, J901.17, J901.20, J901.23, J901.26, J901.29, J901.32, J901.35, J901.38, J901.41, J901.44, J901.47, R922.P$2 (2); also elsewhere on the board
VDD_SERVO_IN: L901.P$2; also elsewhere on the board
VDD_SERVO_SENS: R918.P$1 (1), R919.P$2 (2); also elsewhere on the board

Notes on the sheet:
Servo Header S.Bus interface
S.Bus in/out
Servo outputs
